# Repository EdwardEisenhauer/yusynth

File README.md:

# yusynth
Schematics and gerber files for yusynth project

# About
My friend is a vacuum tube fanatic, so we decided to build a modular synthesizer based on [Yves Usson's project](https://yusynth.net/Modular/index_en.html). As manufacturing of PCBs in China is enormously cheap and trivial in comparison to itching the board in your basement by yourself, we decided to recreate the project in KiCAD and share it with the World.

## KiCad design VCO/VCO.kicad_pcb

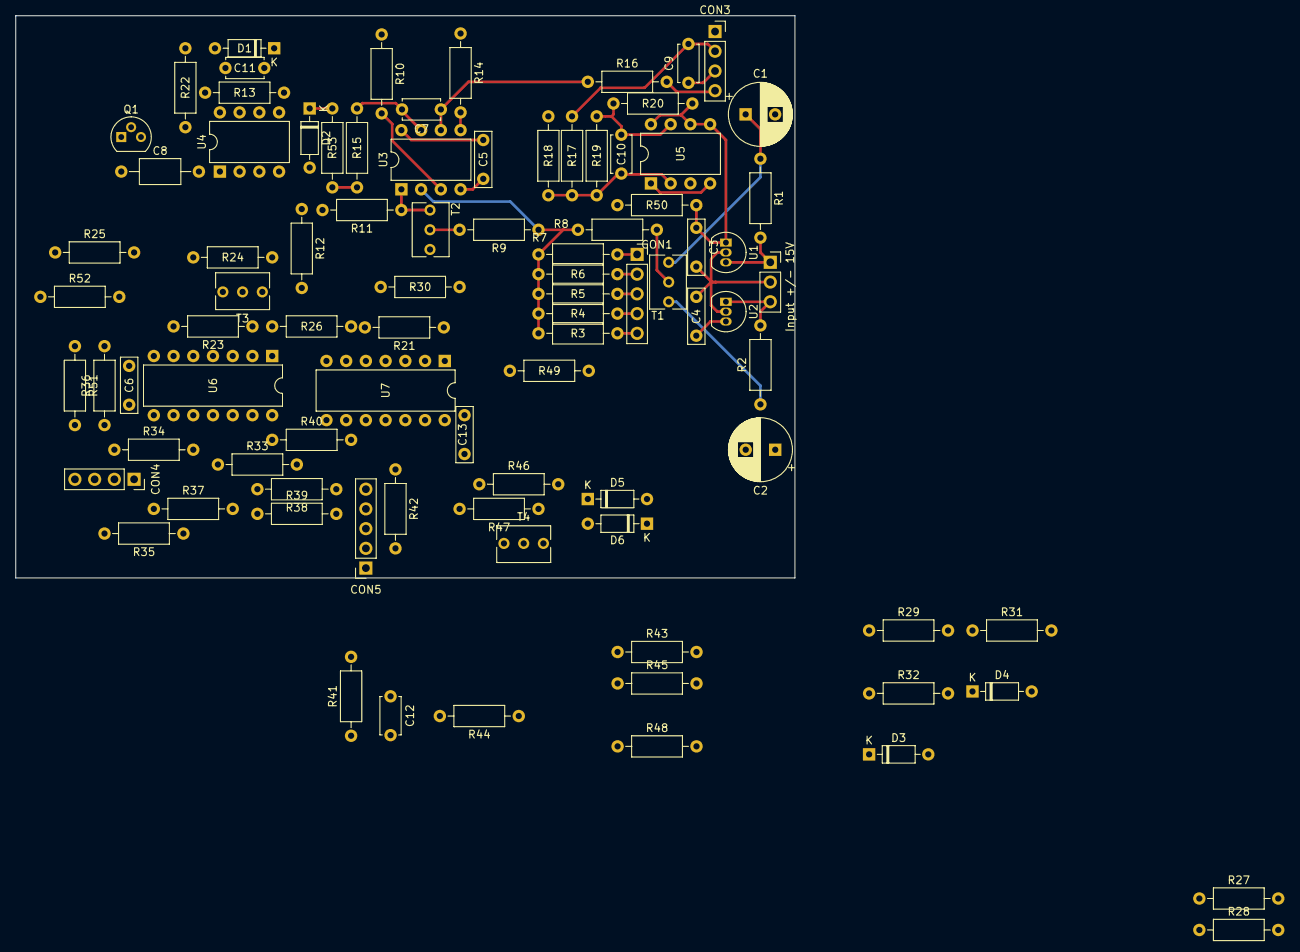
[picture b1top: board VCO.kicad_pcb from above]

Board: 2 copper layers, 100.3 x 72.4 mm, 89 parts (0 on the bottom side), 59 nets.

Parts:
C1, C2: 22u; CP_Radial_D8.0mm_P3.80mm
C3, C4, C5, C6, C13: 100n; C_Rect_L7.0mm_W2.0mm_P5.00mm
C7: 100p; C_Disc_D4.7mm_W2.5mm_P5.00mm
C8: 220pF 1%; C_Axial_L5.1mm_D3.1mm_P10.00mm_Horizontal
C9, C11, C12: 47p; C_Disc_D4.7mm_W2.5mm_P5.00mm
C10: 10p; C_Disc_D4.7mm_W2.5mm_P5.00mm
CON1: Modulation; PinSocket_1x05_P2.54mm_Vertical
CON3: Sync_In; PinSocket_1x04_P2.54mm_Vertical
CON4: PWM input; PinSocket_1x04_P2.54mm_Vertical
CON5: Wave output; PinSocket_1x05_P2.54mm_Vertical
CON6: Input +/- 15V; PinSocket_1x03_P2.54mm_Vertical
D1, D2, D3, D4, D5, D6: 1N4148; D_DO-35_SOD27_P7.62mm_Horizontal
Q1: MMBFJ112; TO-92
R1, R2: 10; R_Axial_DIN0207_L6.3mm_D2.5mm_P10.16mm_Horizontal
R3, R4, R5, R29, R30, R31: 100k 1%; R_Axial_DIN0207_L6.3mm_D2.5mm_P10.16mm_Horizontal
R6: 3M3; R_Axial_DIN0207_L6.3mm_D2.5mm_P10.16mm_Horizontal
R7: 270k; R_Axial_DIN0207_L6.3mm_D2.5mm_P10.16mm_Horizontal
R8, R52: 470k; R_Axial_DIN0207_L6.3mm_D2.5mm_P10.16mm_Horizontal
R9, R20: 33k; R_Axial_DIN0207_L6.3mm_D2.5mm_P10.16mm_Horizontal
R10: 47k; R_Axial_DIN0207_L6.3mm_D2.5mm_P10.16mm_Horizontal
R11: 22k 1%; R_Axial_DIN0207_L6.3mm_D2.5mm_P10.16mm_Horizontal
R12: 1k NTC tempco; R_Axial_DIN0207_L6.3mm_D2.5mm_P10.16mm_Horizontal
R13, R19, R53: 1M; R_Axial_DIN0207_L6.3mm_D2.5mm_P10.16mm_Horizontal
R14, R16, R22, R24, R27, R33, R35, R50: 100k; R_Axial_DIN0207_L6.3mm_D2.5mm_P10.16mm_Horizontal
R15, R17, R18, R21, R28, R37: 10k; R_Axial_DIN0207_L6.3mm_D2.5mm_P10.16mm_Horizontal
R23: 82k/100k; R_Axial_DIN0207_L6.3mm_D2.5mm_P10.16mm_Horizontal
R25: 5k6; R_Axial_DIN0207_L6.3mm_D2.5mm_P10.16mm_Horizontal
R26: 220k 1%; R_Axial_DIN0207_L6.3mm_D2.5mm_P10.16mm_Horizontal
R32: 50k 1%; R_Axial_DIN0207_L6.3mm_D2.5mm_P10.16mm_Horizontal
R34: 180k; R_Axial_DIN0207_L6.3mm_D2.5mm_P10.16mm_Horizontal
R36, R51: 12k; R_Axial_DIN0207_L6.3mm_D2.5mm_P10.16mm_Horizontal
R38: 4k7; R_Axial_DIN0207_L6.3mm_D2.5mm_P10.16mm_Horizontal
R39, R40, R42, R47: 1k; R_Axial_DIN0207_L6.3mm_D2.5mm_P10.16mm_Horizontal
R41: 200k 1%; R_Axial_DIN0207_L6.3mm_D2.5mm_P10.16mm_Horizontal
R43, R44: 150k; R_Axial_DIN0207_L6.3mm_D2.5mm_P10.16mm_Horizontal
R45: 1k5; R_Axial_DIN0207_L6.3mm_D2.5mm_P10.16mm_Horizontal
R46: 15k; R_Axial_DIN0207_L6.3mm_D2.5mm_P10.16mm_Horizontal
R48: 22k; R_Axial_DIN0207_L6.3mm_D2.5mm_P10.16mm_Horizontal
R49: 50k; R_Axial_DIN0207_L6.3mm_D2.5mm_P10.16mm_Horizontal
T1: 220k; Potentiometer_Bourns_3266Y_Vertical
T2: 25k; Potentiometer_Bourns_3266Y_Vertical
T3: 10k; Potentiometer_Bourns_3266Y_Vertical
T4: 47k; Potentiometer_Bourns_3266Y_Vertical
U1: L78L15; TO-92_Inline
U2: L79L15; TO-92_Inline
U3: OPA2137; DIP-8_W7.62mm
U4: LM394CN; DIP-8_W7.62mm
U5: LM311; DIP-8_W7.62mm
U6, U7: TL074; DIP-14_W7.62mm

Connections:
+15V: C1.1, C6.1, C13.1, CON4.2, R1.1, R36.1, R36.2, T1.3, T4.1, U6.4, U7.4
-15V: C2.2, C6.2, C13.2, CON4.4, R2.1, R25.1, R51.1, R51.2, T1.1, U6.11, U7.11
/+15VPS: CON6.1, R1.2, U1.3
/-15VPS: CON6.3, R2.2, U2.1
/COARSE_TUNE: CON1.1, R7.1
/EXP_FM: CON1.5, R3.2
/FINE_TUNE: CON1.2, R6.2
/FMMOD: CON3.4, R16.2
/HARD_SYNC_IN: C9.2, CON3.2, R17.2
/PULSE_OUT: CON5.3, R40.2
/PWM_IN: CON4.1, R34.1
/PW_POT: CON4.3, R35.2
/SAW_OUT: CON5.5, R42.2
/SINE_OUT: CON5.2, R47.2
/SOFT_SYNC_IN: C9.1, CON3.3
/TRI_OUT: CON5.4, R39.2
/V\OCT_IN1: CON1.4, R4.2
/V\OCT_IN2: CON1.3, R5.2
GND: C1.2, C2.1, C3.2, C4.1, CON3.1, CON5.1, CON6.2, D5.1, D6.2, R10.1, R12.2, R14.1, R18.1, R38.1, R45.1, R48.2, R49.2, R52.1, T3.3, T4.3, U1.2, U2.2, U4.5, U6.3, U6.12, U7.5, U7.10
unnamed: C7.1, R13.2, R16.1, U3.6, U4.1
unnamed: C7.2, R15.1, U3.7
unnamed: C8.1, Q1.1, U4.6, U6.5
unnamed: C8.2, Q1.2, R13.1, R22.2, U7.1, U7.2
unnamed: C10.1, R17.1, R18.2, R19.1, U5.2
unnamed: C10.2, C11.1, D1.1, R19.2, R20.1, U5.7
unnamed: C11.2, D1.2, Q1.3, R22.1
unnamed: C12.1, R41.2, R42.1, R43.1, U7.8
unnamed: C12.2, R29.2, R32.2, R41.1, R44.2, U7.9
unnamed: D2.1, R53.2
unnamed: D2.2, R11.2, R12.1, U4.2
unnamed: D3.1, R30.2, R31.1, U7.6
unnamed: D3.2, D4.1, U7.7
unnamed: D4.2, R31.2, R32.1
unnamed: D5.2, D6.1, R43.2, R48.1, U7.12
unnamed: R3.1, R4.1, R5.1, R6.1, R7.2, R8.1, R9.1, U3.2
unnamed: R8.2, T1.2
unnamed: R9.2, T2.2
unnamed: R10.2, U3.3
unnamed: R11.1, T2.1, U3.1
unnamed: R14.2, U3.5
unnamed: R15.2, R53.1, U4.3, U4.4
unnamed: R21.1, U5.3
unnamed: R21.2, R23.2, U6.6, U6.7
unnamed: R23.1, R24.2, R26.1, U6.2
unnamed: R24.1, T3.2
unnamed: R25.2, T3.1
unnamed: R26.2, R27.1, R28.1, R29.1, R30.1, U6.1
unnamed: R27.2, R33.1, U6.13
unnamed: R28.2, U6.9
unnamed: R33.2, R40.1, U6.14
unnamed: R34.2, R35.1, R52.2, U6.10
unnamed: R37.1, U6.8
unnamed: R37.2, R38.2, R39.1
unnamed: R44.1, T4.2
unnamed: R45.2, R46.1, U7.13
unnamed: R46.2, R47.1, U7.14
unnamed: R49.1, R50.2, U7.3
VCC: C3.1, C5.1, R20.2, R50.1, U1.1, U3.8, U5.5, U5.6, U5.8
VSS: C4.2, C5.2, U2.3, U3.4, U5.1, U5.4

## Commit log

2020-10-29 Added .gitignore and introduced VCO schematic
2020-10-30 Modified unpolarised capasitor symbols and added footprints
2020-10-30 Schematic is almost complete
2020-10-30 Introduced a PCB
2020-10-31 Updated .gitignore and added more footprints
2020-10-31 Almost finished the schematic
2020-10-31 circuit diagram updated
2020-11-10 Updated LM394 footprint and placed some elements on the PCB
2020-11-12 Fixed wrong labeled and assigned power ports
2020-11-12 Updated PCB
